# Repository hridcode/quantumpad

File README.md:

# QuantumPad

Hey everyone! This is my submission for Hack Club Blueprint 2026!
This is actually the first hardware project I've designed, and I had a lot of fun making it!

## Features

- 9 MX switches
- Seeed Studio XIAO RP2040 MCU
- KMK firmware
- Rotary encoder + push button
- OLED display

## Images

|Schematic|PCB|Macropad|
|-------|-------|-------|
||||

## Firmware

I just whipped up something quick because I don't really have anything to test it with :/ I might want to upgrade it in the future

## BOM

- 1x Seeed Studio XIAO RP2040 MCU
- 9x Cherry MX Switches
- 1x EC11 rotary encoder
- 1x 0.91" SSD1306 OLED display
- 1x Case (2 3D-printed parts)
- 4x M3x5x4mm heatset inserts
- 4x M3x16mm screws
- 9x through-hole 1N4148 diodes

## Notes

Have fun!

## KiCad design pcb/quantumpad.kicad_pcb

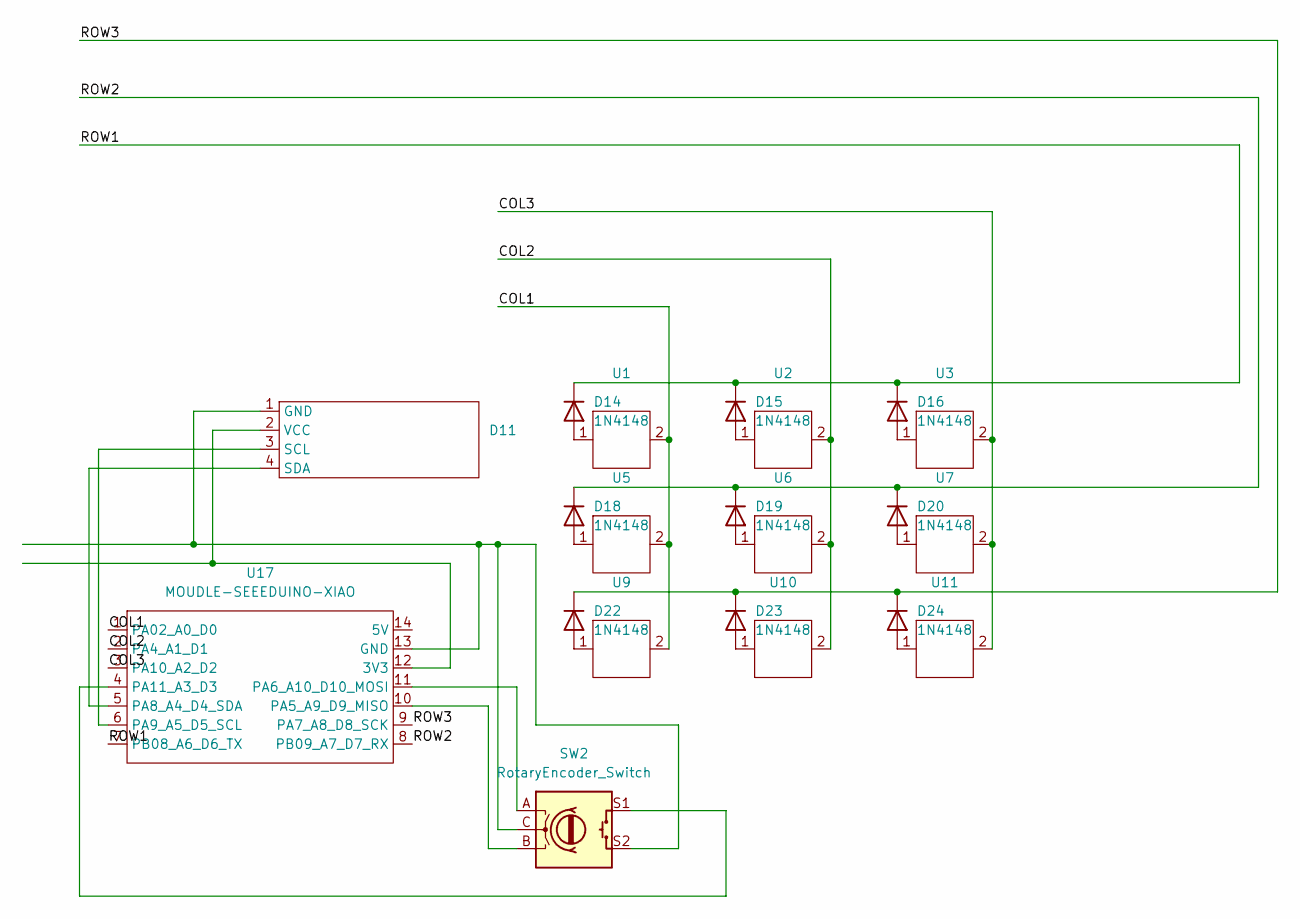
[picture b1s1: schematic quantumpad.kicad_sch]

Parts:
D11: SSD1306-4pin-0.91
D14, D15, D16, D18, D19, D20, D22, D23, D24: 1N4148; D_DO-35_SOD27_P7.62mm_Horizontal
SW2: RotaryEncoder_Switch; RotaryEncoder_Alps_EC11E-Switch_Vertical_H20mm
U1, U2, U3, U5, U6, U7, U9, U10, U11: MX-Solderable-1U
U17: MOUDLE-SEEEDUINO-XIAO; XIAO-RP2040

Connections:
/COL1: U1.2, U5.2, U9.2, U17.1 (PA02_A0_D0)
/COL2: U2.2, U6.2, U10.2, U17.2 (PA4_A1_D1)
/COL3: U3.2, U7.2, U11.2, U17.3 (PA10_A2_D2)
/ROW1: D14.1 (K), D15.1 (K), D16.1 (K), U17.7 (PB08_A6_D6_TX)
/ROW2: D18.1 (K), D19.1 (K), D20.1 (K), U17.8 (PB09_A7_D7_RX)
/ROW3: D22.1 (K), D23.1 (K), D24.1 (K), U17.9 (PA7_A8_D8_SCK)
unnamed: D11.1 (GND), SW2.C, SW2.S2, U17.13 (GND)
unnamed: D11.3 (SCL), U17.6 (PA9_A5_D5_SCL)
unnamed: D11.4 (SDA), U17.5 (PA8_A4_D4_SDA)
unnamed: D11.2 (VCC), U17.12 (3V3)
unnamed: D14.2 (A), U1.1
unnamed: D15.2 (A), U2.1
unnamed: D16.2 (A), U3.1
unnamed: D18.2 (A), U5.1
unnamed: D19.2 (A), U6.1
unnamed: D20.2 (A), U7.1
unnamed: D22.2 (A), U9.1
unnamed: D23.2 (A), U10.1
unnamed: D24.2 (A), U11.1
unnamed: SW2.B, U17.10 (PA5_A9_D9_MISO)
unnamed: SW2.A, U17.11 (PA6_A10_D10_MOSI)
unnamed: SW2.S1, U17.4 (PA11_A3_D3)

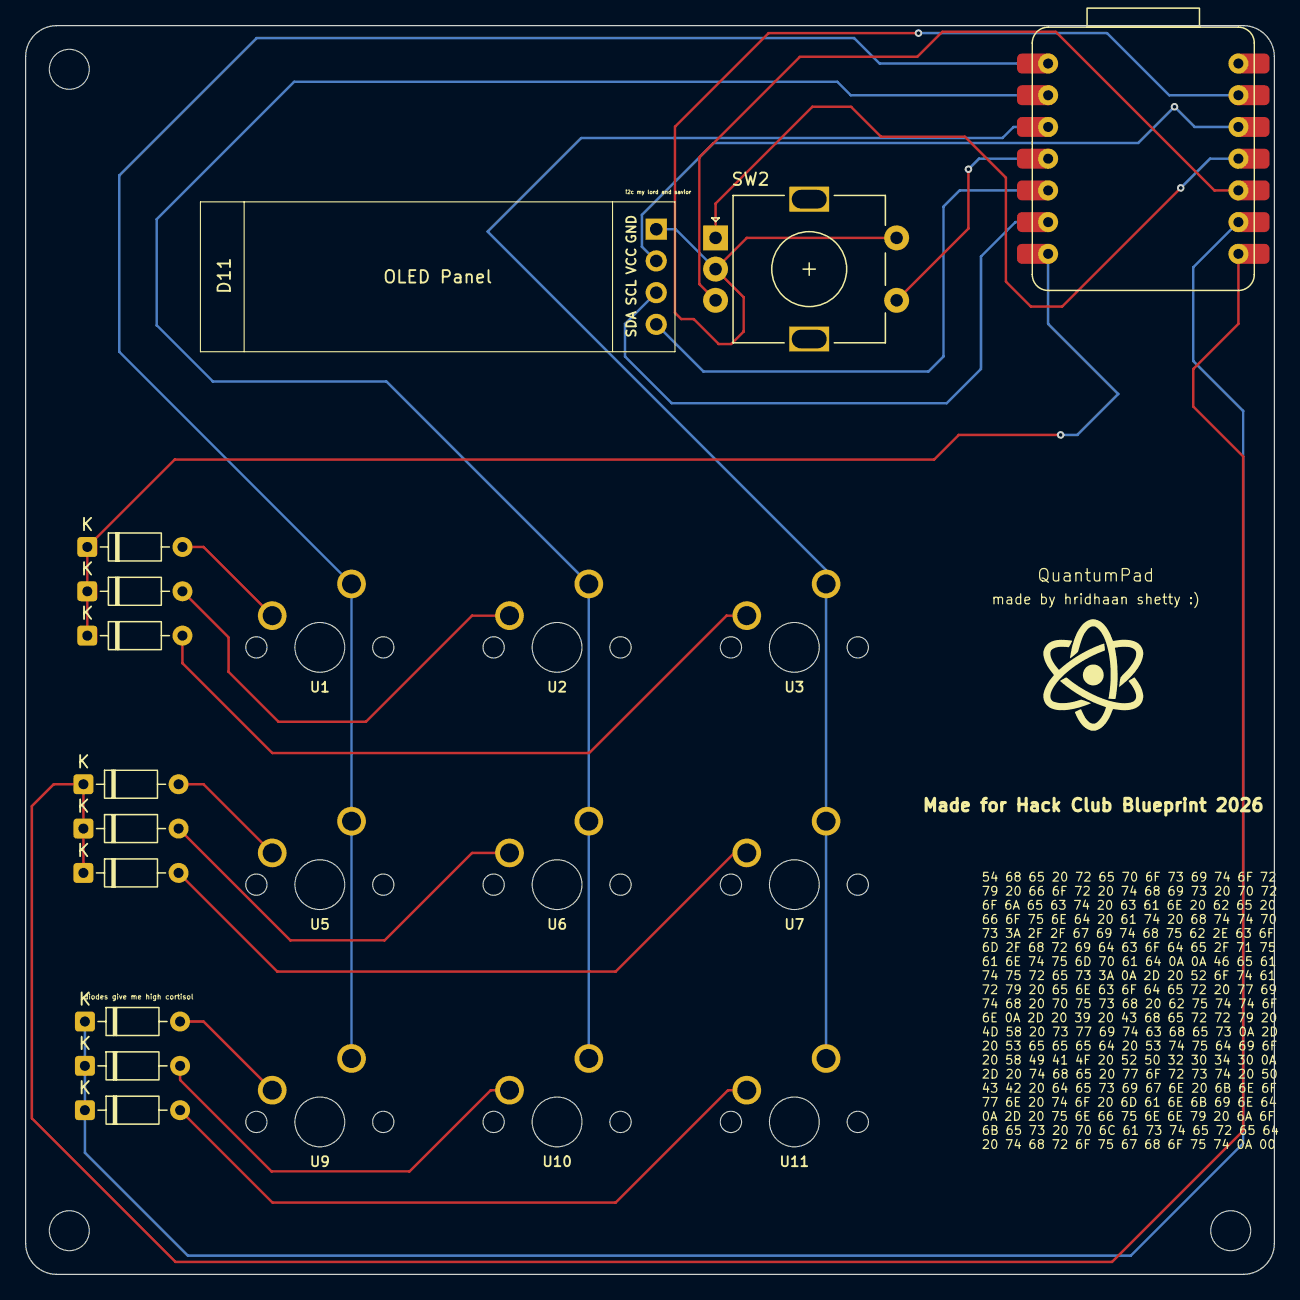
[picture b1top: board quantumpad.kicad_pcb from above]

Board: 2 copper layers, 100.0 x 100.0 mm, 21 parts (0 on the bottom side), 22 nets.

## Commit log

2026-03-03 Added source files
2026-03-04 Added production files
2026-03-04 Added images
2026-03-05 Added .f3z CAD source file
2026-03-05 Added BOM and updated images/PCB/gerber
